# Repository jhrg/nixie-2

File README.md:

Nixie clock code

10/1/22

The current version of this clock software is 0.1.0

A Nixie tube clock using Z573M tubes and a K155N?1 BCD to decimal driver.

This will use multiplexing to drive four Z573M tubes using one K155N?1 chip.

| Timer output | Arduino output	| Chip pin | Pin name |
|--------------|----------------|----------|----------|
|    OC0A	   |        6	    |   12	   |    PD6   |
|    OC0B	   |        5	    |   11	   |    PD5   |
|    OC1A	   |        9	    |   15	   |    PB1   |
|    OC1B	   |        10	    |   16	   |    PB2   |
|    OC2A	   |        11	    |   17	   |    PB3   |
|    OC2B	   |        3	    |   5	   |    PD3   |

*https://docs.arduino.cc/tutorials/generic/secrets-of-arduino-pwm

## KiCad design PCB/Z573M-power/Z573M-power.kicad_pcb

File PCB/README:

What's here?

Z573M-tube is a breakout board for the Z57xM nixie tubes.

breakout-boards are KiCAD footprints for the Adafruit DS3231, BMP-180/280
and the exixe IN-14N nixie tube board.

nixies-2.1 has the KiCAD design files for the nixie-2.1 board

nixie-footprints.pretty holds a number of KiCAD footprints for the
nixie-2.1 PCB.

nixie-tube-clock-2.1.kicad_sym holds (most of) the symbols used by the
nixies-2.1 board.

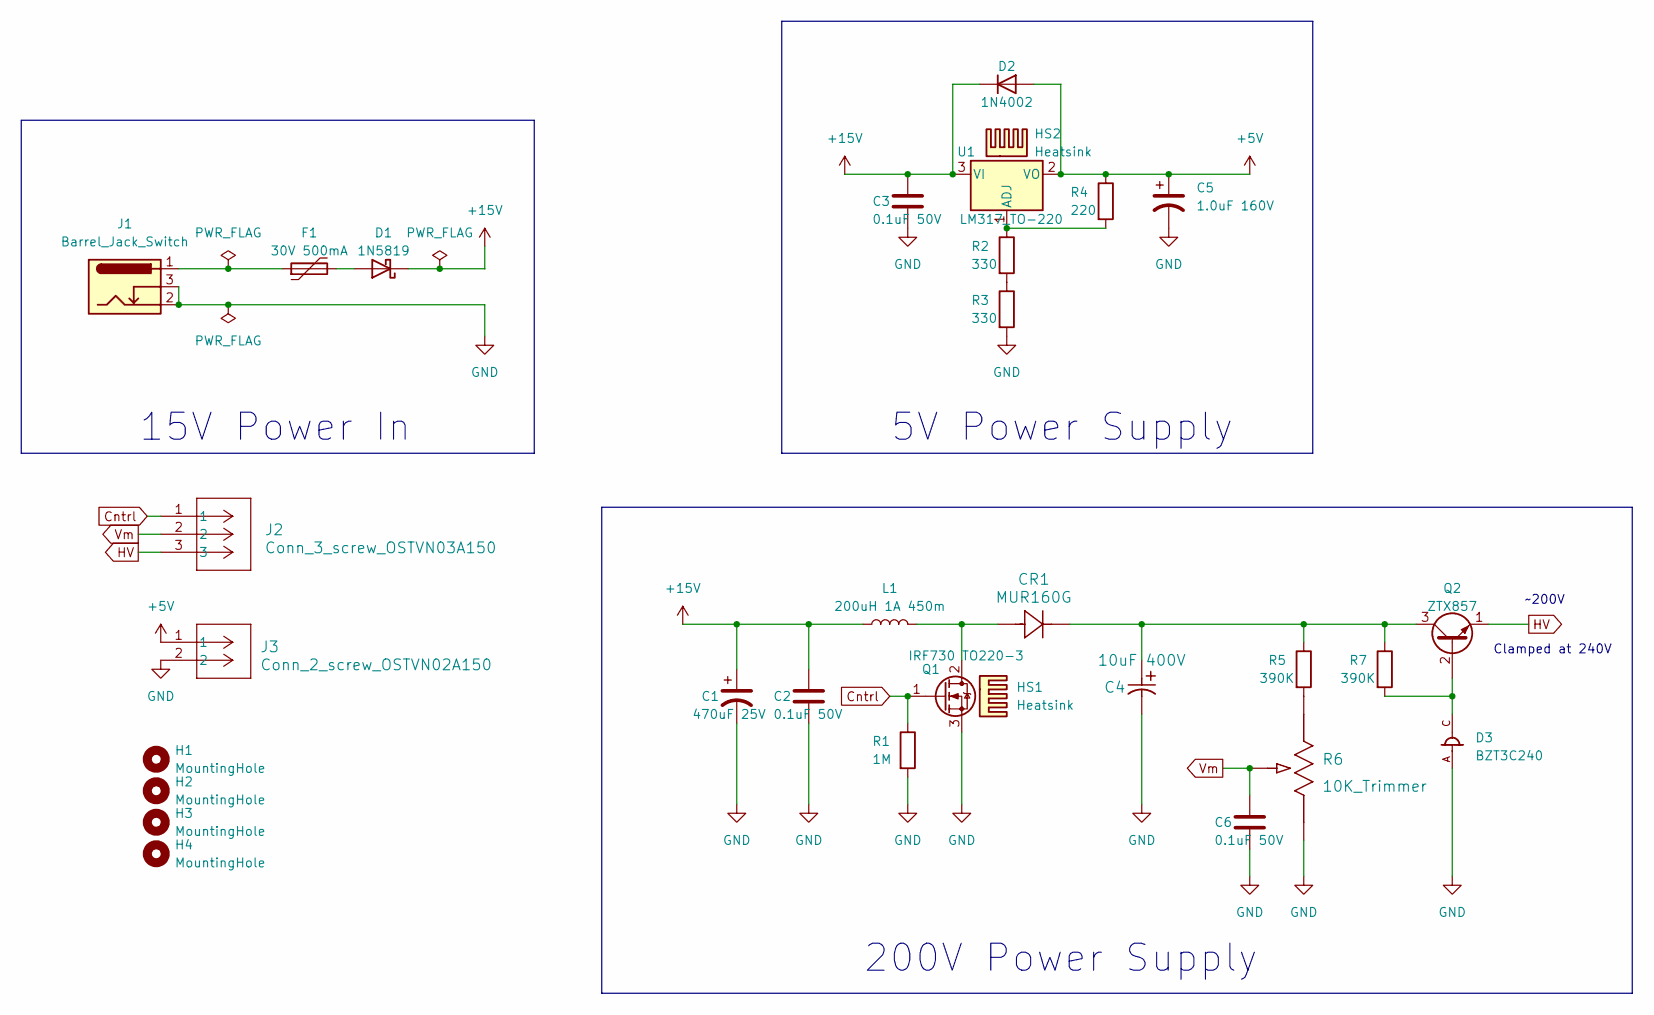
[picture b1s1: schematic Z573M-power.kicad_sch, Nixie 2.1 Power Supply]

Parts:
C1: 470uF 25V; CP_Radial_D10.0mm_P5.00mm
C2, C3, C6: 0.1uF 50V; C_Disc_D5.0mm_W2.5mm_P5.00mm
C4: 10uF 400V; 10uF_400v_ESG106M400AH4AA
C5: 1.0uF 160V; 1.0uF_160V_CAPPRD200W50D525H1250
CR1: MUR160G
D1: 1N5819; D_DO-41_SOD81_P10.16mm_Horizontal
D2: 1N4002; D_A-405_P7.62mm_Horizontal
D3: BZT3C240
F1: 30V 500mA; AHRF050_30v_500mA_polyfuse
H1, H2, H3, H4: MountingHole; MountingHole_3mm
HS1, HS2: Heatsink; AVVID-577202B-00000G
J1: Barrel_Jack_Switch; BarrelJack_Horizontal
J2: Conn_3_screw_OSTVN03A150; CONN3_OSTVN03A150_OST
J3: Conn_2_screw_OSTVN02A150; CONN_OSTVN02A150_OST
L1: 200uH 1A 450m; L_Radial_D7.8mm_P5.00mm_Fastron_07HCP
Q1: IRF730 TO220-3; TO-220-3_Vertical
Q2: ZTX857; TO-92_HandSolder
R1: 1M; R_Axial_DIN0207_L6.3mm_D2.5mm_P7.62mm_Horizontal
R2, R3: 330; R_Axial_DIN0207_L6.3mm_D2.5mm_P7.62mm_Horizontal
R4: 220; R_Axial_DIN0207_L6.3mm_D2.5mm_P7.62mm_Horizontal
R5, R7: 390K; R_Axial_DIN0207_L6.3mm_D2.5mm_P7.62mm_Horizontal
R6: 10K_Trimmer; 10k_Trimmer_PV36W103C01B00
U1: LM317_TO-220; TO-220-3_Vertical

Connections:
+5V: C5.1, D2.2 (A), J3.1, R4.1, U1.2 (VO)
+15V: C1.1, C2.1, C3.1, D1.1 (K), D2.1 (K), L1.1, U1.3 (VI)
Cntrl: J2.1, Q1.1 (G), R1.1
GND: C1.2, C2.2, C3.2, C4.2, C5.2, C6.2, D3.A, J1.2, J1.3, J3.2, Q1.3 (S), R1.2, R3.2, R6.1
HV: J2.3, Q2.1 (E)
unnamed: D1.2 (A), F1.2
unnamed: F1.1, J1.1
unnamed: CR1.2, L1.2, Q1.2 (D)
unnamed: D3.C, Q2.2 (B), R7.2
unnamed: C4.1, CR1.1, Q2.3 (C), R5.1, R7.1
unnamed: R2.2, R3.1
unnamed: R5.2, R6.3
unnamed: R2.1, R4.2, U1.1 (ADJ)
Vm: C6.1, J2.2, R6.2

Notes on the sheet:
5V Power Supply
~200V
200V Power Supply
15V Power In
Clamped at 240V

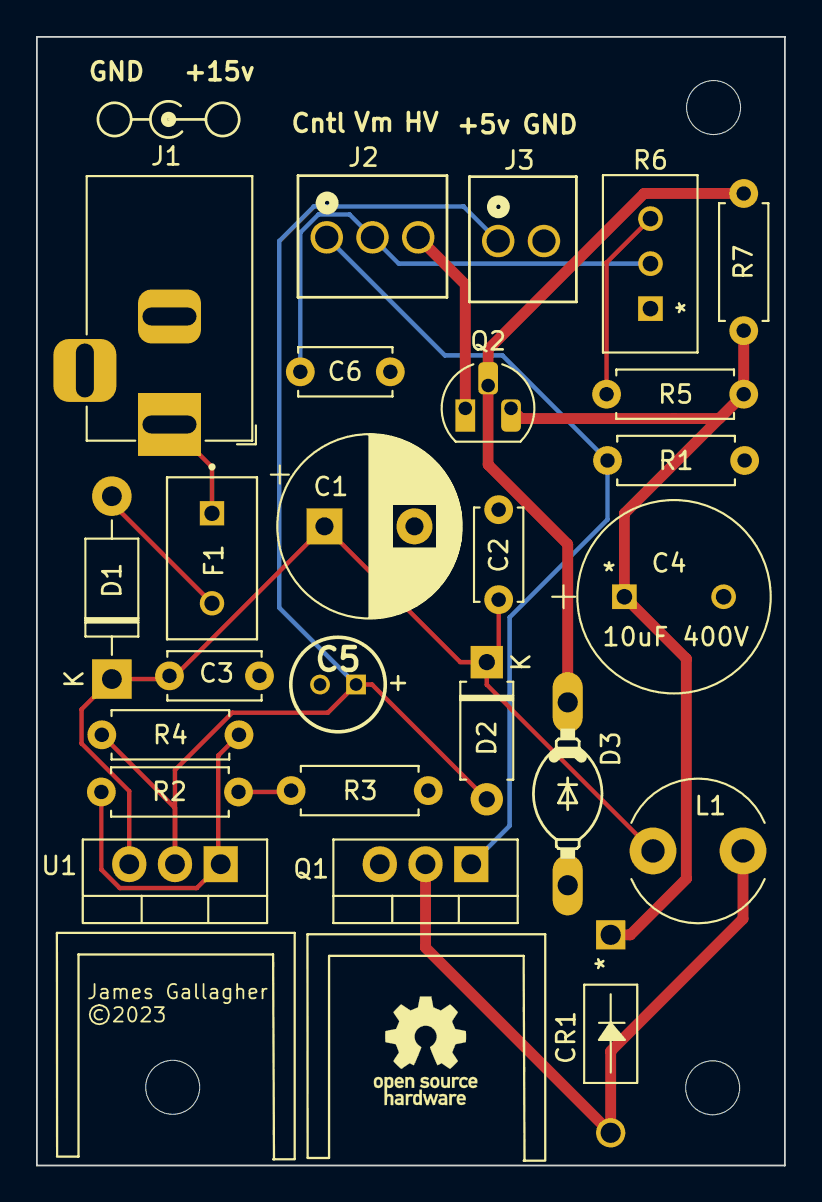
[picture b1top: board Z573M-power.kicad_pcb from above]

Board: 2 copper layers, 41.6 x 62.7 mm, 30 parts (0 on the bottom side), 14 nets.

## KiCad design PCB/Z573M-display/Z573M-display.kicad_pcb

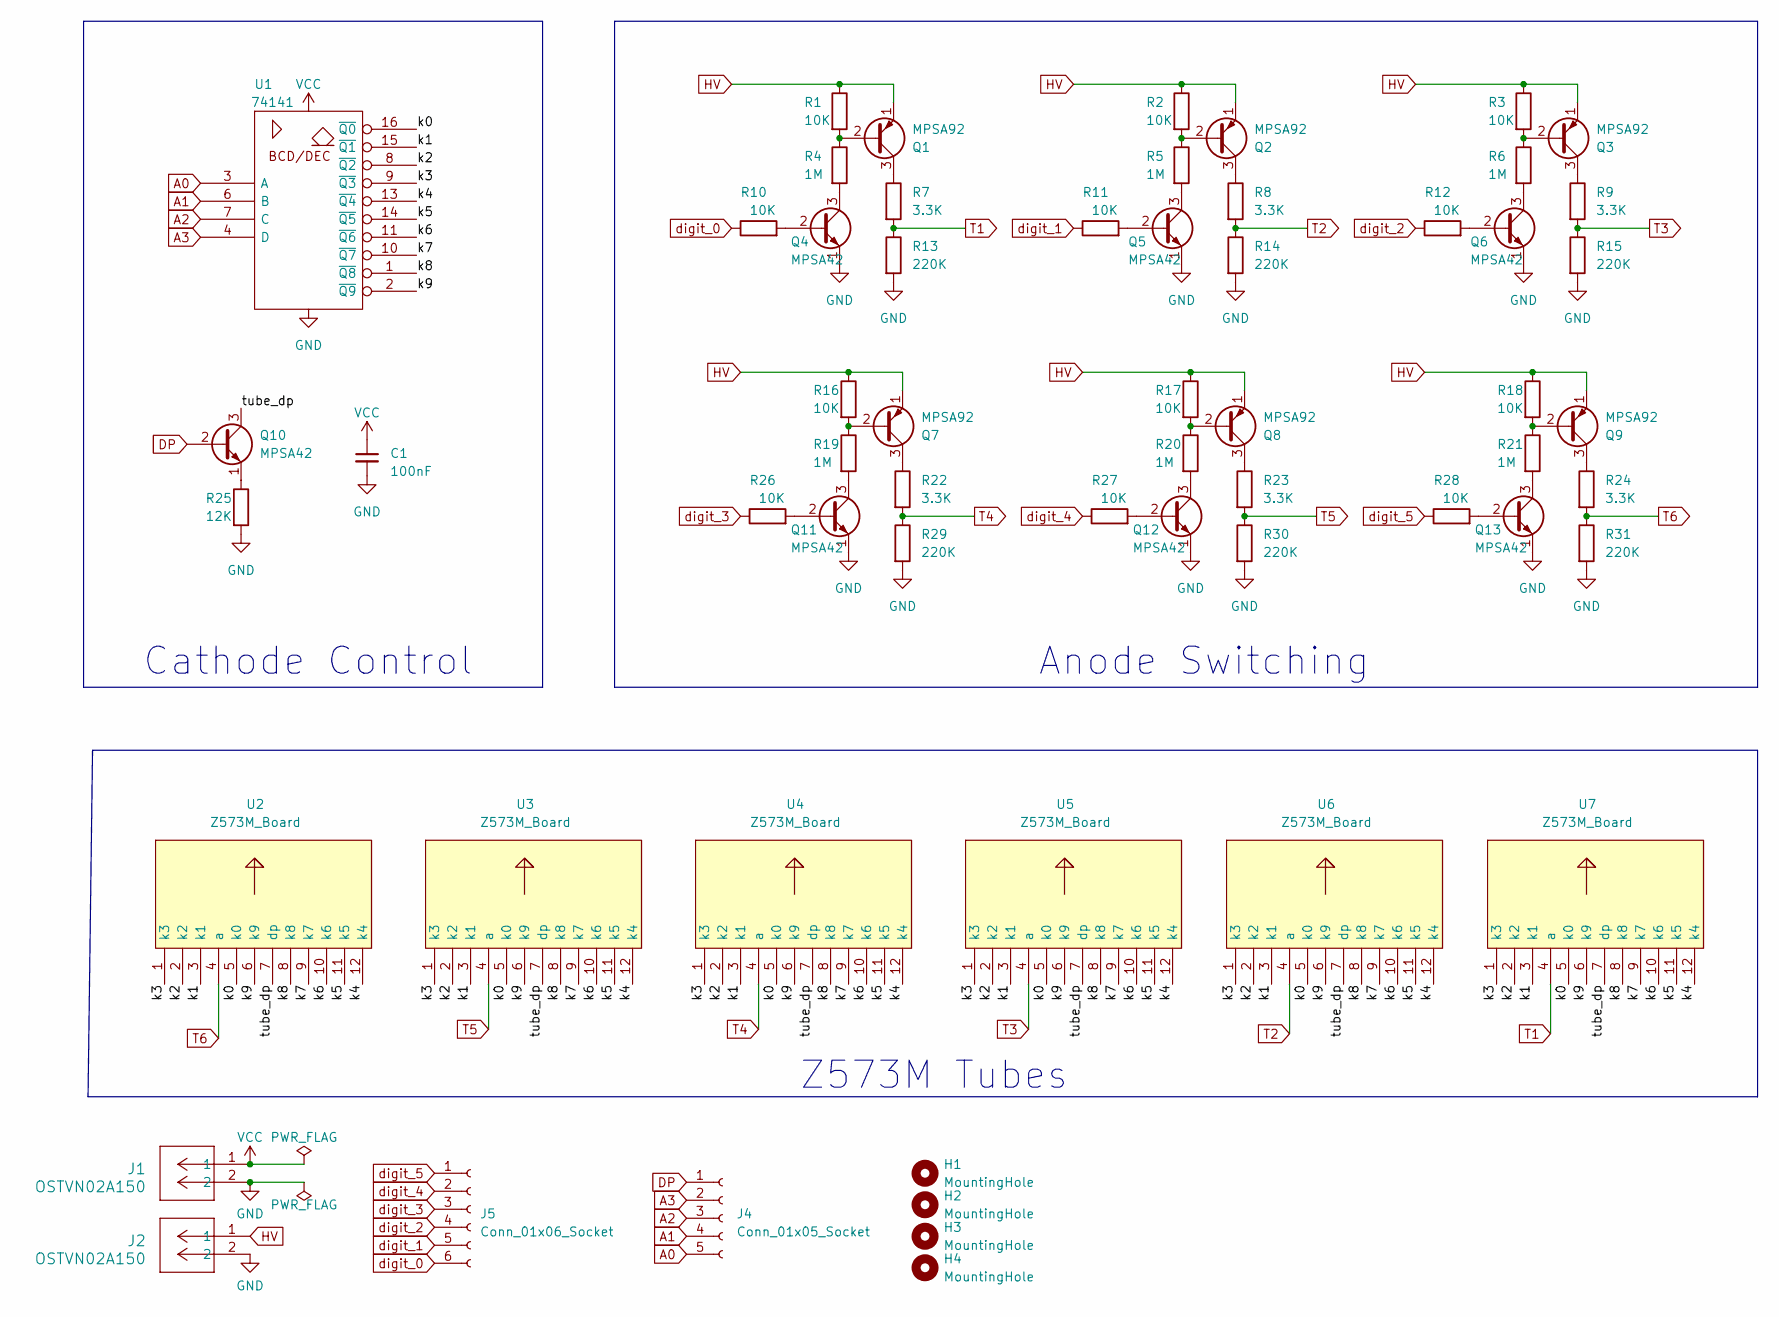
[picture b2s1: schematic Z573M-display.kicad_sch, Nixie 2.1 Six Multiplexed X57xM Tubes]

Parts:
C1: 100nF; C_Disc_D4.7mm_W2.5mm_P5.00mm
H1, H2, H3, H4: MountingHole; MountingHole_3mm
J1, J2: OSTVN02A150; CONN_OSTVN02A150_OST
J4: Conn_01x05_Socket; PinHeader_1x05_P2.54mm_Horizontal
J5: Conn_01x06_Socket; PinHeader_1x06_P2.54mm_Horizontal
Q1, Q2, Q3, Q7, Q8, Q9: MPSA92; TO-92_HandSolder
Q4, Q5, Q6, Q10, Q11, Q12, Q13: MPSA42; TO-92_HandSolder
R1, R2, R3, R10, R11, R12, R16, R17, R18, R26, R27, R28: 10K; R_Axial_DIN0207_L6.3mm_D2.5mm_P7.62mm_Horizontal
R4, R5, R6, R19, R20, R21: 1M; R_Axial_DIN0207_L6.3mm_D2.5mm_P7.62mm_Horizontal
R7, R8, R9, R22, R23, R24: 3.3K; R_Axial_DIN0207_L6.3mm_D2.5mm_P7.62mm_Horizontal
R13, R14, R15, R29, R30, R31: 220K; R_Axial_DIN0207_L6.3mm_D2.5mm_P7.62mm_Horizontal
R25: 12K; R_Axial_DIN0207_L6.3mm_D2.5mm_P7.62mm_Horizontal
U1: 74141; DIP-16_W7.62mm_Socket
U2, U3, U4, U5, U6, U7: Z573M_Board

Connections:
/k0: U1.16 (~Q0), U2.5 (k0), U3.5 (k0), U4.5 (k0), U5.5 (k0), U6.5 (k0), U7.5 (k0)
/k1: U1.15 (~Q1), U2.3 (k1), U3.3 (k1), U4.3 (k1), U5.3 (k1), U6.3 (k1), U7.3 (k1)
/k2: U1.8 (~Q2), U2.2 (k2), U3.2 (k2), U4.2 (k2), U5.2 (k2), U6.2 (k2), U7.2 (k2)
/k3: U1.9 (~Q3), U2.1 (k3), U3.1 (k3), U4.1 (k3), U5.1 (k3), U6.1 (k3), U7.1 (k3)
/k4: U1.13 (~Q4), U2.12 (k4), U3.12 (k4), U4.12 (k4), U5.12 (k4), U6.12 (k4), U7.12 (k4)
/k5: U1.14 (~Q5), U2.11 (k5), U3.11 (k5), U4.11 (k5), U5.11 (k5), U6.11 (k5), U7.11 (k5)
/k6: U1.11 (~Q6), U2.10 (k6), U3.10 (k6), U4.10 (k6), U5.10 (k6), U6.10 (k6), U7.10 (k6)
/k7: U1.10 (~Q7), U2.9 (k7), U3.9 (k7), U4.9 (k7), U5.9 (k7), U6.9 (k7), U7.9 (k7)
/k8: U1.1 (~Q8), U2.8 (k8), U3.8 (k8), U4.8 (k8), U5.8 (k8), U6.8 (k8), U7.8 (k8)
/k9: U1.2 (~Q9), U2.6 (k9), U3.6 (k9), U4.6 (k9), U5.6 (k9), U6.6 (k9), U7.6 (k9)
/tube_dp: Q10.3 (C), U2.7 (dp), U3.7 (dp), U4.7 (dp), U5.7 (dp), U6.7 (dp), U7.7 (dp)
A0: J4.5, U1.3 (A)
A1: J4.4, U1.6 (B)
A2: J4.3, U1.7 (C)
A3: J4.2, U1.4 (D)
DP: J4.1, Q10.2 (B)
GND: C1.2, J1.2, J2.2, Q4.1 (E), Q5.1 (E), Q6.1 (E), Q11.1 (E), Q12.1 (E), Q13.1 (E), R13.2, R14.2, R15.2, R25.2, R29.2, R30.2, R31.2, U1.12 (GND)
HV: J2.1, Q1.1 (E), Q2.1 (E), Q3.1 (E), Q7.1 (E), Q8.1 (E), Q9.1 (E), R1.1, R2.1, R3.1, R16.1, R17.1, R18.1
unnamed: Q1.2 (B), R1.2, R4.1
unnamed: Q1.3 (C), R7.1
unnamed: Q2.2 (B), R2.2, R5.1
unnamed: Q2.3 (C), R8.1
unnamed: Q3.2 (B), R3.2, R6.1
unnamed: Q3.3 (C), R9.1
unnamed: Q4.2 (B), R10.2
unnamed: Q4.3 (C), R4.2
unnamed: Q5.2 (B), R11.2
unnamed: Q5.3 (C), R5.2
unnamed: Q6.2 (B), R12.2
unnamed: Q6.3 (C), R6.2
unnamed: Q7.2 (B), R16.2, R19.1
unnamed: Q7.3 (C), R22.1
unnamed: Q8.2 (B), R17.2, R20.1
unnamed: Q8.3 (C), R23.1
unnamed: Q9.2 (B), R18.2, R21.1
unnamed: Q9.3 (C), R24.1
unnamed: Q10.1 (E), R25.1
unnamed: Q11.2 (B), R26.2
unnamed: Q11.3 (C), R19.2
unnamed: Q12.2 (B), R27.2
unnamed: Q12.3 (C), R20.2
unnamed: Q13.2 (B), R28.2
unnamed: Q13.3 (C), R21.2
T1: R7.2, R13.1, U7.4 (a)
T2: R8.2, R14.1, U6.4 (a)
T3: R9.2, R15.1, U5.4 (a)
T4: R22.2, R29.1, U4.4 (a)
T5: R23.2, R30.1, U3.4 (a)
T6: R24.2, R31.1, U2.4 (a)
VCC: C1.1, J1.1, U1.5 (VCC)
digit_0: J5.6, R10.1
digit_1: J5.5, R11.1
digit_2: J5.4, R12.1
digit_3: J5.3, R26.1
digit_4: J5.2, R27.1
digit_5: J5.1, R28.1

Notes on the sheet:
Z573M Tubes
Anode Switching
Cathode Control

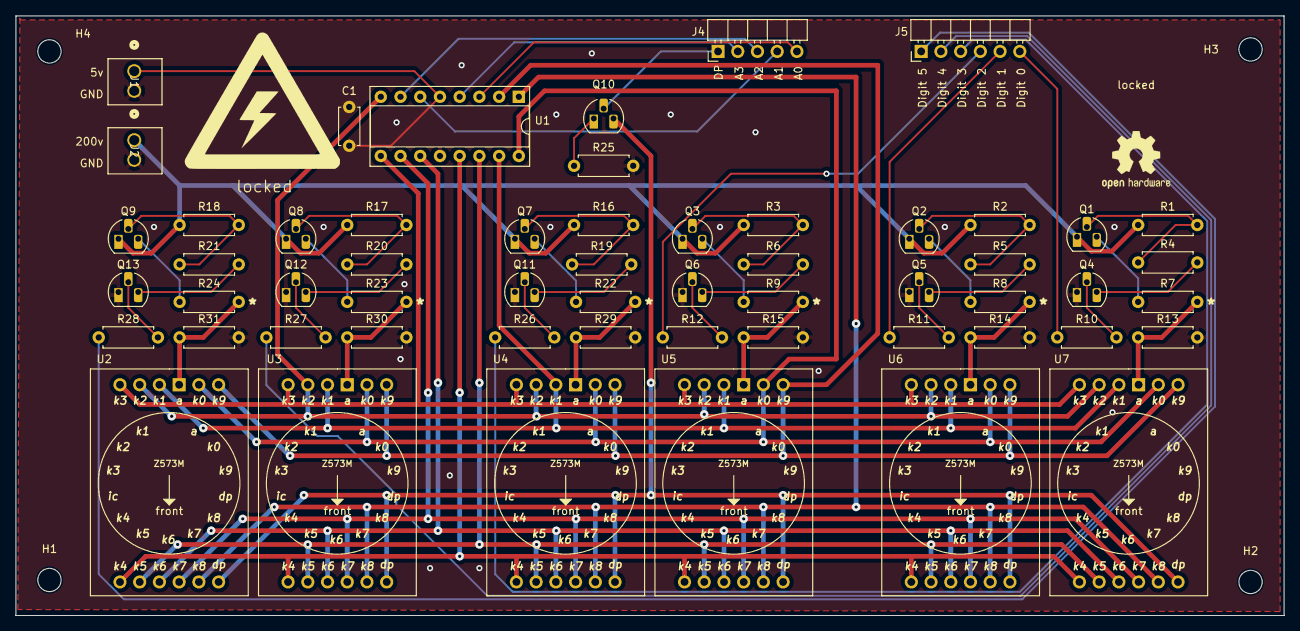
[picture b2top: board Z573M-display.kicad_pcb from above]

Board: 2 copper layers, 163.3 x 77.2 mm, 60 parts (0 on the bottom side), 56 nets.

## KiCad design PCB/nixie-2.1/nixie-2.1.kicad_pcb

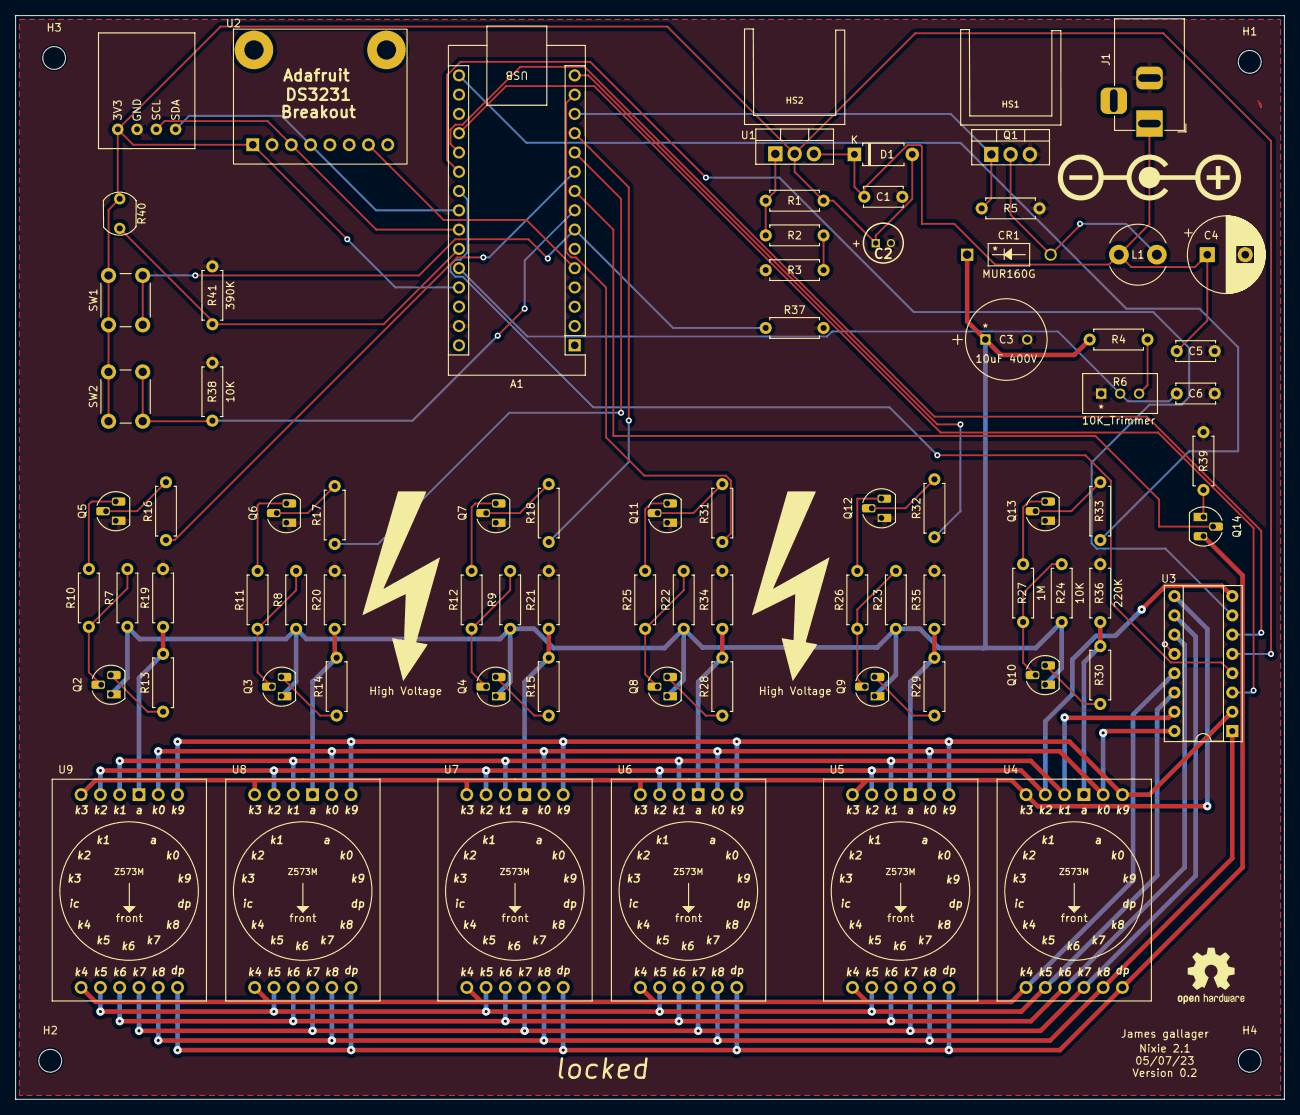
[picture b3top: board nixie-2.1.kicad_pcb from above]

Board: 2 copper layers, 167.1 x 142.7 mm, 84 parts (0 on the bottom side), 69 nets.

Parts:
A1: Arduino_Nano_v3.x; Arduino_Nano
C1, C5, C6: 0.1uF 50V; C_Disc_D5.0mm_W2.5mm_P5.00mm
C2: 1.0uF 160V; 1.0uF_160V_CAPPRD200W50D525H1250
C3: 10uF 400V; ESG475M400AH2AA
C4: 470uF 25V; CP_Radial_D10.0mm_P5.00mm
CR1: MUR160G
D1: 1N4002; D_A-405_P7.62mm_Horizontal
H1, H2, H3, H4: MountingHole; MountingHole_3mm
HS1, HS2: Heatsink; AVVID-577202B-00000G
J1: Barrel_Jack_Switch; BarrelJack_Horizontal
L1: 200uH 1A 450m; L_Radial_D7.8mm_P5.00mm_Fastron_07HCP
Q1: IRF730 TO220-3; TO-220-3_Vertical
Q2, Q3, Q4, Q8, Q9, Q10: MPSA92; TO-92_HandSolder
Q5, Q6, Q7, Q11, Q12, Q13, Q14: MPSA42; TO-92_HandSolder
R1: 220; R_Axial_DIN0207_L6.3mm_D2.5mm_P7.62mm_Horizontal
R2, R3: 330; R_Axial_DIN0207_L6.3mm_D2.5mm_P7.62mm_Horizontal
R4, R41: 390K; R_Axial_DIN0207_L6.3mm_D2.5mm_P7.62mm_Horizontal
R5, R10, R11, R12, R25, R26, R27: 1M; R_Axial_DIN0207_L6.3mm_D2.5mm_P7.62mm_Horizontal
R6: 10K_Trimmer; PV36W103C01B00
R7, R8, R9, R16, R17, R18, R22, R23, R24, R31, R32, R33, R37, R38: 10K; R_Axial_DIN0207_L6.3mm_D2.5mm_P7.62mm_Horizontal
R13, R14, R15, R28, R29, R30: 3.3K; R_Axial_DIN0207_L6.3mm_D2.5mm_P7.62mm_Horizontal
R19, R20, R21, R34, R35, R36: 220K; R_Axial_DIN0207_L6.3mm_D2.5mm_P7.62mm_Horizontal
R39: 12K; R_Axial_DIN0207_L6.3mm_D2.5mm_P7.62mm_Horizontal
R40: R_Photo; R_LDR_5.1x4.3mm_P3.9mm_Vertical
SW1, SW2: SW_Push; SW_PUSH_6mm
U1: LM317_TO-220; TO-220-3_Vertical
U2: Adafruit_DS3231_breakout
U3: 74141; DIP-16_W7.62mm_Socket
U4, U5, U6, U7, U8, U9: Z573M_Board
U10: BMP180_breakout; BMP280_bb

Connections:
1s_pulse: A1.5 (D2), U2.7 (SQW)
+5V: A1.27 (+5V), C2.1, D1.2 (A), R1.1, R40.1, SW1.1, SW2.1, U1.2 (VO), U2.1 (Vin), U3.5 (VCC), U10.1 (Vin)
+15V: C1.1, C4.1, C5.1, D1.1 (K), J1.1, L1.1, U1.3 (VI)
/Nixies 2.1 Display/k0: U3.16 (~Q0), U4.5 (k0), U5.5 (k0), U6.5 (k0), U7.5 (k0), U8.5 (k0), U9.5 (k0)
/Nixies 2.1 Display/k1: U3.15 (~Q1), U4.3 (k1), U5.3 (k1), U6.3 (k1), U7.3 (k1), U8.3 (k1), U9.3 (k1)
/Nixies 2.1 Display/k2: U3.8 (~Q2), U4.2 (k2), U5.2 (k2), U6.2 (k2), U7.2 (k2), U8.2 (k2), U9.2 (k2)
/Nixies 2.1 Display/k3: U3.9 (~Q3), U4.1 (k3), U5.1 (k3), U6.1 (k3), U7.1 (k3), U8.1 (k3), U9.1 (k3)
/Nixies 2.1 Display/k4: U3.13 (~Q4), U4.12 (k4), U5.12 (k4), U6.12 (k4), U7.12 (k4), U8.12 (k4), U9.12 (k4)
/Nixies 2.1 Display/k5: U3.14 (~Q5), U4.11 (k5), U5.11 (k5), U6.11 (k5), U7.11 (k5), U8.11 (k5), U9.11 (k5)
/Nixies 2.1 Display/k6: U3.11 (~Q6), U4.10 (k6), U5.10 (k6), U6.10 (k6), U7.10 (k6), U8.10 (k6), U9.10 (k6)
/Nixies 2.1 Display/k7: U3.10 (~Q7), U4.9 (k7), U5.9 (k7), U6.9 (k7), U7.9 (k7), U8.9 (k7), U9.9 (k7)
/Nixies 2.1 Display/k8: U3.1 (~Q8), U4.8 (k8), U5.8 (k8), U6.8 (k8), U7.8 (k8), U8.8 (k8), U9.8 (k8)
/Nixies 2.1 Display/k9: U3.2 (~Q9), U4.6 (k9), U5.6 (k9), U6.6 (k9), U7.6 (k9), U8.6 (k9), U9.6 (k9)
/Nixies 2.1 Display/tube_dp: Q14.3 (C), U4.7 (dp), U5.7 (dp), U6.7 (dp), U7.7 (dp), U8.7 (dp), U9.7 (dp)
A0: A1.19 (A0), U3.3 (A)
A1: A1.20 (A1), U3.6 (B)
A2: A1.21 (A2), U3.7 (C)
A3: A1.22 (A3), U3.4 (D)
Cntrl: A1.13 (D10), Q1.1 (G), R5.1
DP: A1.9 (D6), Q14.2 (B)
GND: A1.4 (GND), A1.29 (GND), C1.2, C2.2, C3.2, C4.2, C5.2, C6.2, J1.2, Q1.3 (S), Q5.1 (E), Q6.1 (E), Q7.1 (E), Q11.1 (E), Q12.1 (E), Q13.1 (E), R3.2, R5.2, R6.1, R19.2, R20.2, R21.2, R34.2, R35.2, R36.2, R37.2, R38.2, R39.2, R41.2, U2.2 (GND), U3.12 (GND), U10.2 (GND)
HV: C3.1, CR1.1, Q2.1 (E), Q3.1 (E), Q4.1 (E), Q8.1 (E), Q9.1 (E), Q10.1 (E), R4.1, R7.1, R8.1, R9.1, R22.1, R23.1, R24.1
unnamed: A1.25 (A6), R40.2, R41.1
unnamed: A1.7 (D4), R37.1, SW1.2
unnamed: A1.8 (D5), R38.1, SW2.2
unnamed: CR1.2, L1.2, Q1.2 (D)
unnamed: Q2.2 (B), R7.2, R10.1
unnamed: Q2.3 (C), R13.1
unnamed: Q3.2 (B), R8.2, R11.1
unnamed: Q3.3 (C), R14.1
unnamed: Q4.2 (B), R9.2, R12.1
unnamed: Q4.3 (C), R15.1
unnamed: Q5.2 (B), R16.2
unnamed: Q5.3 (C), R10.2
unnamed: Q6.2 (B), R17.2
unnamed: Q6.3 (C), R11.2
unnamed: Q7.2 (B), R18.2
unnamed: Q7.3 (C), R12.2
unnamed: Q8.2 (B), R22.2, R25.1
unnamed: Q8.3 (C), R28.1
unnamed: Q9.2 (B), R23.2, R26.1
unnamed: Q9.3 (C), R29.1
unnamed: Q10.2 (B), R24.2, R27.1
unnamed: Q10.3 (C), R30.1
unnamed: Q11.2 (B), R31.2
unnamed: Q11.3 (C), R25.2
unnamed: Q12.2 (B), R32.2
unnamed: Q12.3 (C), R26.2
unnamed: Q13.2 (B), R33.2
unnamed: Q13.3 (C), R27.2
unnamed: Q14.1 (E), R39.1
unnamed: R2.2, R3.1
unnamed: R4.2, R6.3
unnamed: R1.2, R2.1, U1.1 (ADJ)
SCL: A1.24 (A5), U2.3 (SCL), U10.3 (SCL)
SDA: A1.23 (A4), U2.4 (SDA), U10.4 (SDA)
T1: R13.2, R19.1, U9.4 (a)
T2: R14.2, R20.1, U8.4 (a)
T3: R15.2, R21.1, U7.4 (a)
T4: R28.2, R34.1, U6.4 (a)
T5: R29.2, R35.1, U5.4 (a)
T6: R30.2, R36.1, U4.4 (a)
Vm: A1.26 (A7), C6.1, R6.2
digit_0: A1.10 (D7), R16.1
digit_1: A1.11 (D8), R17.1
digit_2: A1.12 (D9), R18.1
digit_3: A1.14 (D11), R31.1
digit_4: A1.15 (D12), R32.1
digit_5: A1.16 (D13), R33.1

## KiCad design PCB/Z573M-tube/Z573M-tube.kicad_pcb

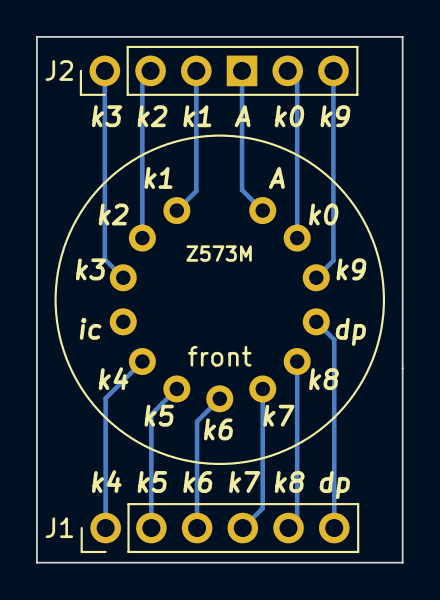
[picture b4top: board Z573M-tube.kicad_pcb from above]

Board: 2 copper layers, 20.3 x 29.2 mm, 3 parts (0 on the bottom side), 12 nets.

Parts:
J1, J2: 6-pin-header; PinHeader_1x06_P2.54mm_Vertical
Version 2.0: Z57xM; Z57xM-v3-HV

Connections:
/A: J2.4, Version 2.0.13 (A)
/K0: J2.5, Version 2.0.12 (K0)
/K1: J2.3, Version 2.0.1 (K1)
/K2: J2.2, Version 2.0.2 (K2)
/K3: J2.1, Version 2.0.3 (K3)
/K4: J1.1, Version 2.0.5 (K4)
/K5: J1.2, Version 2.0.6 (K5)
/K6: J1.3, Version 2.0.7 (K6)
/K7: J1.4, Version 2.0.8 (K7)
/K8: J1.5, Version 2.0.9 (K8)
/K9: J2.6, Version 2.0.11 (K9)
/KPR: J1.6, Version 2.0.10 (KPR)

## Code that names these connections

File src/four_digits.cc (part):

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
// All of the digits are on PORTB (D8 - D15). This means there
// can be no SPI bus use.
#define DIGIT_0 B00000001 // D8
#define DIGIT_1 B00000010 // D9
#define DIGIT_2 B00000100 // D10
#define DIGIT_3 B00001000 // D11
#define DIGIT_4 B00010000 // D12
#define DIGIT_5 B00100000 // D13

// PORTD, the decimal points
#define RHDP B10000000 // D7
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
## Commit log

2022-10-02 Added code to display a BCD digit and to control anode current
2022-10-02 Added .gitignore
2022-10-02 Added info from the scope and modified the code to use multiplexing.
    The code simulates six digits even though I used on two on the hardware.
2022-10-03 Added more measurements
    Not sure about the scope voltage measurements
2022-10-03 Now uses port registers for faster I/O
2022-10-03 cleanup
2022-10-07 Addd more info about multiplexing
    100Hz - no increase in tube voltage; decrease Ra to 4.k
    and tube voltage increases from 148v to 155v
2022-10-09 Changed the digit timing - 50uS blanking
2022-10-09 New ports for BCD and digits
2022-10-10 Added the DS3231 clock
2022-10-10 minor re-org
2022-10-11 This version uses the DS3231 SQW output at 1Hz to trigger the clock read
2022-10-11 Change the clock library - WIP
2022-10-13 Changed images to r/w only
2022-10-14 Added more scope pictures
2022-10-14 Added ripple picture
2022-10-16 Switched DS3231 library to the Adafruit one
2022-10-16 Fixed the display of minutes...hours (was all seconds
2022-10-17 Fixed use of timer2 - now the times are correct.
    Digit on time is 900uS and blanking is 50uS
2022-10-17 Organization of the scope pictures
2022-10-17 Added todo comments
2022-10-17 Mode todos for stuff in the ISR code
2022-10-18 Added one more scope picture
2022-10-18 Consolodated ISR and digit display
2022-10-18 Streamline the main ISR - avoid changing the TIMER2 CS2n bits.
2022-10-18 Works - the time spent in the ISR dropped to 3.4 and 1.6uS
    ...from 4.7 and 1.5uS
2022-10-19 Added Eagle footprint library
2022-10-20 Swapped out the a promini for the nano and a DS1307 for the DS3231
    Burned up the nano and the DS3231. Also increased the blanking time
    to 100uS.
2022-10-23 Works but with lots of jitter
2022-10-24 Added symbols
2022-10-24 Added info about nixie libs
2022-10-30 Added files for a PCB
2022-10-30 Switch to DS3231
2022-10-30 DS3231 fix
2022-10-30 Only access the clock every CLOCK_QUERY_INTERVAL s
2022-10-30 fixed time update
2022-10-30 Fixed uodate off by one error
2022-10-31 Removed old code
2022-10-31 Don't call update_time() when about to read from the clock
2022-11-01 Added mode switch initial version
2022-11-01 Fixed the mode switch code
2022-11-01 Mode switch changes
2022-11-01 Added state enums
2022-11-01 Added INPUT MODE Switch
2022-11-01 input switch ISRs
2022-11-01 input switch fixes
2022-11-01 Fixes for the inout switch
2022-11-02 Adding date mode - WIP
2022-11-02 Another try at debouncing the input switch
2022-11-02 Time & Date mode - date years are wrong
2022-11-02 fix the year 10's digit
2022-11-02 Added DHT 'weather' info
2022-11-02 More updates
    Changes to prevent display flash on boot didn't work.
2022-11-03 Minor edits - comments, etc.
2022-11-03 Factor DHT sensor code out
2022-11-03 Use the new library for the DHT sensor
2022-11-03 Added non-blocking DHT library
2022-11-05 Added MPL3115A2 for barometric pressure info
2022-11-05 Test the MPL3115A2
2022-11-05 minor debug
2022-11-05 Interrupts are stopped while reading from MPL3115A2 - FAIL
2022-11-05 Fix interrupts issue for MPL3115A2 - maybe other stuff
2022-11-05 Fixes for the weather display
    Increased on time to 4s for each of temp/rh and pressure
2022-11-05 Various updates for the pressure display
2022-11-05 Altitude correction for pressure measurement
2022-11-05 Added initial version of decimal point control
2022-11-06 Actual decimal point support
2022-11-06 Added blank_dp()
2022-11-06 There is no left hand decimal point on the Z537M
2022-11-06 Added DST code (not used). Better initial time value.
2022-11-08 set-time WIP
2022-11-08 removed non-blocking DHT code
2022-11-08 Added picture of voltage over Ra
2022-11-09 symbols and footprints
2022-11-09 New symbols
2022-11-09 More libraries
2022-11-10 Changes to gitignore
2022-11-10 set time WIP
2022-11-10 New Z570M Footprint
2022-11-11 Mode switch maddness
2022-11-11 Now uses 115200 baud
2022-11-11 factor main_mode_update out of loop
2022-11-11 Added simple time set option
2022-11-11 Fixed basic time set mode
2022-11-11 More mode madness
2022-11-11 WIP - super fast is silly
2022-11-12 Refactor
2022-11-12 Better time setting mode. Still, the seconds are lacking...
2022-11-12 more cleanup
2022-11-12 Changed buttons to active high with pull down res
2022-11-12 Added potential fix for temp/humidity failure
2022-11-12 Start on adding date set
2022-11-13 Started on date
2022-11-13 Ignore stuff in PCB for now
2022-11-13 Added code to set the date
2022-11-13 tweak the year setting
2022-11-13 Added newline to messages
2022-11-13 Date set works
2022-11-14 Fix for the DHT sensor failure to read issue
2022-11-14 Display fix
2022-11-15 minor edits
2022-11-16 change interrupt to pin 5
2022-11-16 more interrupt change
2022-11-17 Need the 'new' nano bootloader for these knockoff nano boards
2022-11-19 Added DP control
2022-11-19 Added digit DPs when in set time mode
2022-11-19 Exit DP display when leaving set time mode
2022-11-19 Comment
2022-11-19 DP fixes ans hacks
    blinks during date, used for weather
2022-11-20 four_digits to six_digits
2022-11-20 Added brightness control
    Use the input button in the main mode to cycle the five levels of
    brightness
2022-11-20 Changed use Serial.print() to new print(), etc., code
2022-11-20 Added new print code files
2022-11-20 New print-fix branch
    The original one did not work.
2022-11-20 Includes correct code to handle F()
2022-11-20 Try adding support for the F() macro
2022-11-21 print and debug macors handle F()
2022-11-21 Compile option to remove DHT22 sensor
2022-11-21 Drop the DHT22...
2022-11-23 More print fixes
2022-11-24 Reset the timer2 counter to zero in the ISR
    This improves the flicker, but does not fix it.
    Also did more work on the debug printing.
    Removed the DHT22.
2022-11-27 Uses timer 1 for multiplexing
2022-11-27 Clean house
2022-11-27 Timer 1 works.
    Debugging the dim display flicker.
2022-11-27 Debug output on
    Not using Serial had no effect on the flicker when display was dim
2022-11-28 minor changes
2022-11-28 Clean up - no more flicker
2022-11-28 printf for floats
2022-11-29 comments
2022-12-03 Added Z573M-tube Schematic and PCB
2022-12-03 Cleaning house
2022-12-03 Use the BME280 sensor
2022-12-03 Added build option for the MPL3115A2
2022-12-07 Added hv_ps.cc
2022-12-08 Added fork of br3ttb/Arduino-PID-Library
2022-12-09 Removed lame attempt to use my PID library fork.
    Now use the lib/fork via a submodule in the lib dir.
2022-12-09 Removed the PCB dir
2022-12-09 Changed the analog port to A7
2022-12-21 Added Z573M PCB
2022-12-21 Pads and design rules
2023-01-01 New board, v 2.0, with gerber files
2023-01-12 Info about timer pins
2023-01-12 PCB updates for Z573M breakout
2023-01-13 Z573M PCB files added
2023-01-13 README improvements
2023-01-15 Start with digit 0
2023-01-15 moved digit 0 to pin 7, opens up pin 10 for HV PS PWM
2023-01-15 minor fix in the set-time mode
2023-01-15 Added Timer 1 code back into the hv_ps.cc file; commented out for now.
2023-01-15 Fix the timer interrupt for this version
2023-01-16 Fixes for the timer switch. Display now refreshes at 160Hz
2023-01-16 HV_PS PWN pin now works
2023-01-16 comments, etc. in the HV PS code
2023-01-16 Use the new HV PS code - WIP
2023-01-16 Added .DS_Store to gitignore
2023-01-30 Remove the MPL3115A2
2023-01-30 Changes for the BME280
2023-01-31 Fixed the pressure calculation
2023-01-31 Temp and RH now have only one significant digit.
2023-02-01 Added ambient light sensor. Conflicts with the input switch setting.
2023-02-05 Bumped up the max output to 200 for hv_ps.cc
2023-02-07 Better comment in platformio.ini
2023-02-08 Added FLIR pictures
2023-02-09 Spelling fix
2023-02-09 Spelling, comments
2023-02-09 Removed docs/Trash
2023-02-09 Added bright/dim digit pairs for set mode feedback
2023-02-09 Spelling in a function name
2023-02-11 Removed interrupt off/on that broke the mode buttons
2023-02-11 Added new function to clear the mode & input switch state
2023-02-11 Removed some DEBUG code
2023-02-11 Refactor how the mode switch state is computed.
2023-02-11 WIP: the input switch
2023-02-12 input switch refactor
2023-02-12 debug text fix
2023-02-12 set input_switch_down_time to now, not zero when the button is released.
2023-02-12 Remove debugging
2023-02-12 Use the pin level, not the interrupt. Assume interrupts might not be correct.
2023-02-12 Removed unused input switch bools
2023-02-12 More old code removal
2023-02-12 Removed #if 0 and fixed DST_offset.cc
2023-04-24 Added PCB work
2023-04-24 Update version info on board
2023-04-25 PCB Stuff
2023-04-26 hacking
2023-04-30 Reorganization
2023-05-10 New display-only board
2023-05-13 Horizontal pins
2023-05-13 Updated PCB with horizontal pin headers and better footprint silkscreens
2023-06-06 updated z573M-logic - try using the zip version
2023-08-22 Added power board
2023-08-22 Display and logic board edits
2023-08-22 Added QR code for power board
2023-08-22 Added QR code to power board
2023-08-22 Added nixie-footprints-pretty
2023-08-23 Updated some traces
2023-08-31 Added the Z573M power BOM
2023-10-05 Added enclosure and updates to the HV PS
2024-08-31 Fixed hv_ps.cc comments which were for an older version of controller

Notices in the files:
PCB/Z573M-power/Z573M-power.kicad_pcb:
©2023
parts and their libraries:
Copyright 2021 Accelerated Designs. All rights reserved.
